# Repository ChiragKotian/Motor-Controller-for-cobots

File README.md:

# Motor-Controller-for-cobots

## Check out presentation.pdf(https://github.com/ChiragKotian/Motor-Controller-for-cobots/blob/main/presentation.pdf) for complete details

### _NOTE_: The final circuit shown in the schematics doesn't contain any protection for the inductive nature of the motor. Be sure to implement them before using this circuit or else you might end-up damaging your controller. 

## Credits

_This project was entirely done by Chirag Kotian (https://github.com/ChiragKotian) as a 'Pre-internship assignment' for PrimaInnotech. If you want to use my work, you are free to do so; don't forget to mention my GitHub page: https://github.com/ChiragKotian._

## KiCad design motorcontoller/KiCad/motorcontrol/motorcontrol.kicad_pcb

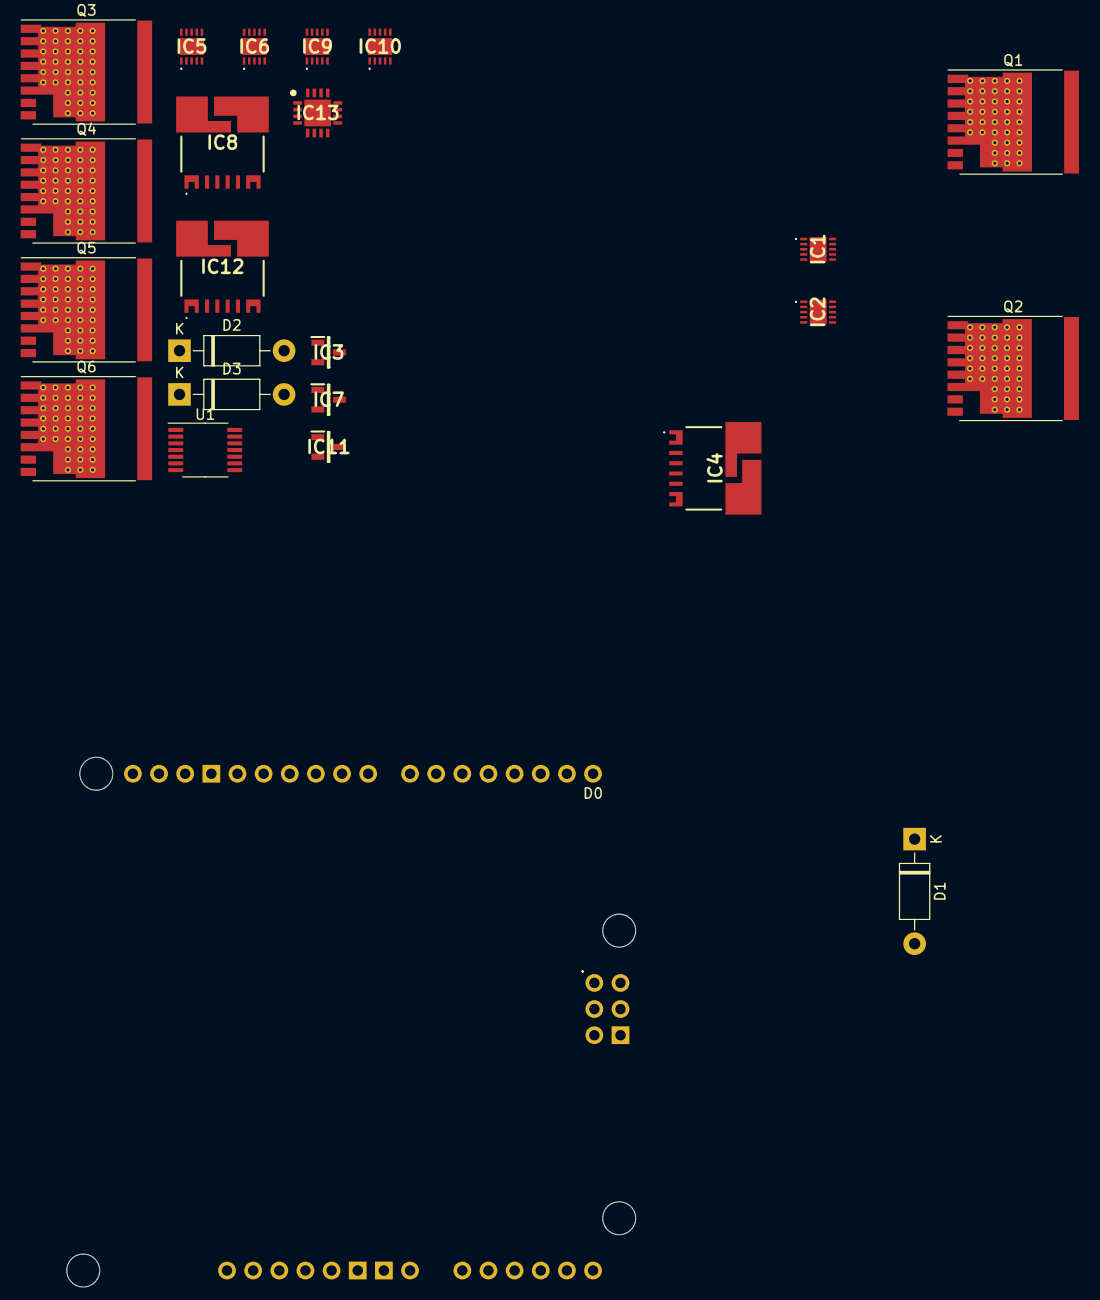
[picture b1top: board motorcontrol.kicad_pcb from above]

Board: 2 copper layers, 24 parts (0 on the bottom side), 42 nets, no tracks yet.

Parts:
A2: Arduino_Uno_R4_Minima_Shield
D1, D2, D3: 1N4001; D_DO-41_SOD81_P10.16mm_Horizontal
IC1, IC2, IC5, IC6, IC9, IC10: 1EDN7126GXTMA1
IC3, IC7, IC11: TMP236AQDBZTQ1; SOT95P237X112-3N
IC4, IC8, IC12: TLI4971A075T5UE0001XUMA1
IC13: TMUX6211RUMR; QFN65P400X400X80-17N-D
Q1, Q2, Q3, Q4, Q5, Q6: IGT60R070D1; Infineon_PG-HSOF-8-3_ThermalVias
U1: AS5048B; TSSOP-14_4.4x5mm_P0.65mm

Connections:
+7.5V: A2.VIN, IC2.6 (VDD), IC6.6 (VDD), IC10.6 (VDD)
+48V: Q1.4 (D), Q3.4 (D), Q5.4 (D)
/A0: A2.A0, IC4.3 (VREF)
/A1: A2.A1, IC3.2 (VOUT)
/A2: A2.A2, IC13.1 (S1), IC13.4 (S4), IC13.9 (S3), IC13.12 (S2)
/A2_1: IC8.3 (VREF), IC13.16 (D1)
/A3_1: IC7.2 (VOUT), IC13.13 (D2)
/A4: A2.A4, U1.1 (SDA)
/A4_1: IC12.3 (VREF), IC13.8 (D3)
/A5: A2.A5, U1.2 (SCL)
/A5_1: IC11.2 (VOUT), IC13.5 (D4)
/D1: A2.D1 (D1/TX), IC13.7 (SEL3)
/D3: A2.D3, IC1.4 (IN+)
/D4: A2.D4, IC8.6 (OCD2_1)
/D5: A2.D5, IC2.4 (IN+)
/D6: A2.D6, IC5.4 (IN+)
/D7: A2.D7, IC12.6 (OCD2_1)
/D8: A2.D8, IC13.15 (SEL1)
/D9: A2.D9, IC6.4 (IN+)
/D10: A2.D10, IC9.4 (IN+)
/D11: A2.D11, IC10.4 (IN+)
/D12: A2.D12, IC13.14 (SEL2)
/D13: A2.D13, IC13.6 (SEL4)
/V3.3: A2.3V3 (3.3V), IC4.1 (VDD_1), IC8.1 (VDD_1), IC12.1 (VDD_1)
/V5: A2.5V1 (5V), IC3.1 (VDD), IC7.1 (VDD), IC11.1 (VDD), IC13.11 (VDD), IC13.17 (EP), U1.11 (VDD5V)
GND: A2.GND1 (GND), A2.GND2 (GND), A2.GND3 (GND), A2.GND4 (SPI_GND), IC1.5 (IN-), IC2.5 (IN-), IC2.11 (VSS), IC3.3 (GND), IC4.2 (GND), IC5.5 (IN-), IC6.5 (IN-), IC6.11 (VSS), IC7.3 (GND), IC8.2 (GND), IC9.5 (IN-), IC10.5 (IN-), IC10.11 (VSS), IC11.3 (GND), IC12.2 (GND), IC13.3 (GND), Q2.1 (S), Q4.1 (S), Q6.1 (S), U1.13 (GND)
unnamed: D1.2 (A), IC2.7 (BST)
unnamed: D1.1 (K), IC1.6 (VDD)
unnamed: D2.2 (A), IC6.7 (BST)
unnamed: D2.1 (K), IC5.6 (VDD)
unnamed: D3.2 (A), IC10.7 (BST)
unnamed: D3.1 (K), IC9.6 (VDD)
unnamed: IC1.8 (OUT_SNK), Q1.3 (G)
unnamed: IC1.11 (VSS), IC4.8 (IP+_1), Q1.1 (S), Q2.4 (D)
unnamed: IC2.8 (OUT_SNK), Q2.3 (G)
unnamed: A2.D2, IC4.6 (OCD2_1)
unnamed: IC5.8 (OUT_SNK), Q3.3 (G)
unnamed: IC5.11 (VSS), IC8.8 (IP+_1), Q3.1 (S), Q4.4 (D)
unnamed: IC6.8 (OUT_SNK), Q4.3 (G)
unnamed: IC9.8 (OUT_SNK), Q5.3 (G)
unnamed: IC10.8 (OUT_SNK), Q6.3 (G)
unnamed: IC9.11 (VSS), IC12.8 (IP+_1), Q5.1 (S), Q6.4 (D)
